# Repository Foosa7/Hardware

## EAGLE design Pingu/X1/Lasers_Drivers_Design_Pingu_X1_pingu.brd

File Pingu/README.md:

# Constant current sources #

* X1 - LED2001PHR, 4A, Buck

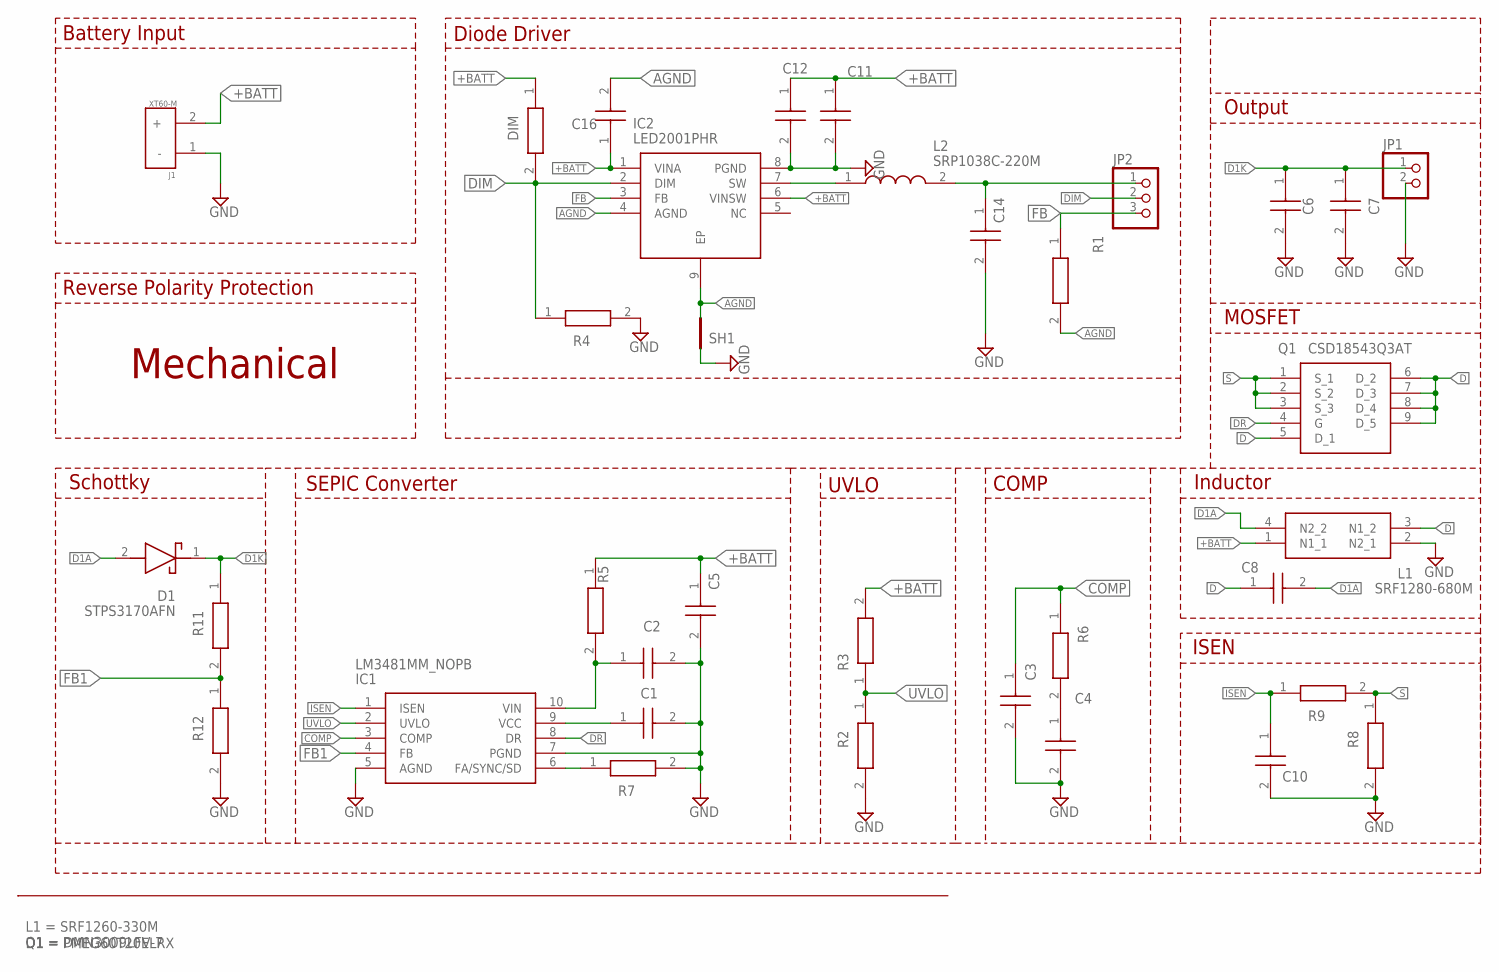
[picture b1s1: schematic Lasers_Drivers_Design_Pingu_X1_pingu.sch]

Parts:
C1, C2, C3, C4, C10, C11, C12: GCM0335C1H8R0DA16J; CAPC0603X33N
C5, C6, C7, C8, C14, C16: C1206C475K5RACTU; CAPC3216X180N
D1: STPS3170AFN; SODFL5226X110N
DIM: ERJ-3BWFR100V; RESC1608X55N
IC1: LM3481MM_NOPB; SOP50P490X110-10N
IC2: LED2001PHR; SOIC127P600X170-9N
J1: XT60-M; AMASS_XT60-M
JP1: PINHD-1X2; 1X02
JP2: PINHD-1X3; 1X03
L1: SRF1280-680M; SRF1280680M
L2: SRP1038C-220M; INDPM110100X420N
Q1: CSD18543Q3AT
R1, R2, R3, R4, R5, R6, R7, R8, R9, R11, R12: ERJ-3BWFR100V; RESC1608X55N
SH1: SHORTT5; SHORT_TOP-50

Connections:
+BATT: C5.1, C11.1, C12.1, C16.1, DIM.1, IC2.1 (VINA), IC2.6 (VINSW), J1.2 (+), L1.1 (N1_1), R3.2, R5.1
AGND: C16.2, IC2.4 (AGND), IC2.9 (EP), R1.2, SH1.2
COMP: C3.1, IC1.3 (COMP), R6.1
D: C8.1, L1.3 (N1_2), Q1.5 (D_1), Q1.6 (D_2), Q1.7 (D_3), Q1.8 (D_4), Q1.9 (D_5)
D1A: C8.2, D1.2 (A), L1.4 (N2_2)
D1K: C6.1, C7.1, D1.1 (K), JP1.1, R11.1
DIM: DIM.2, IC2.2 (DIM), JP2.2, R4.1
DR: IC1.8 (DR), Q1.4 (G)
FB: IC2.3 (FB), JP2.3, R1.1
FB1: IC1.4 (FB), R11.2, R12.1
GND: C1.2, C2.2, C3.2, C4.2, C5.2, C6.2, C7.2, C10.2, C11.2, C12.2, C14.2, IC1.5 (AGND), IC1.7 (PGND), IC2.8 (PGND), J1.1 (-), JP1.2, L1.2 (N2_1), R2.2, R4.2, R7.2, R8.2, R12.2, SH1.1
ISEN: C10.1, IC1.1 (ISEN), R9.1
unnamed: C1.1, IC1.9 (VCC)
unnamed: C4.1, R6.2
unnamed: IC2.7 (SW), L2.1
unnamed: IC1.6 (FA/SYNC/SD), R7.1
unnamed: C2.1, IC1.10 (VIN), R5.2
unnamed: C14.1, JP2.1, L2.2
S: Q1.1 (S_1), Q1.2 (S_2), Q1.3 (S_3), R8.1, R9.2
UVLO: IC1.2 (UVLO), R2.1, R3.1

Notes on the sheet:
L1 = SRF1260-330M
Battery Input
Reverse Polarity Protection
Q1 = DMN3009LFV-7
D1 = PMEG60T20ELRX
Diode Driver
Mechanical
UVLO
COMP
ISEN
SEPIC Converter
Inductor
MOSFET
Output
Schottky

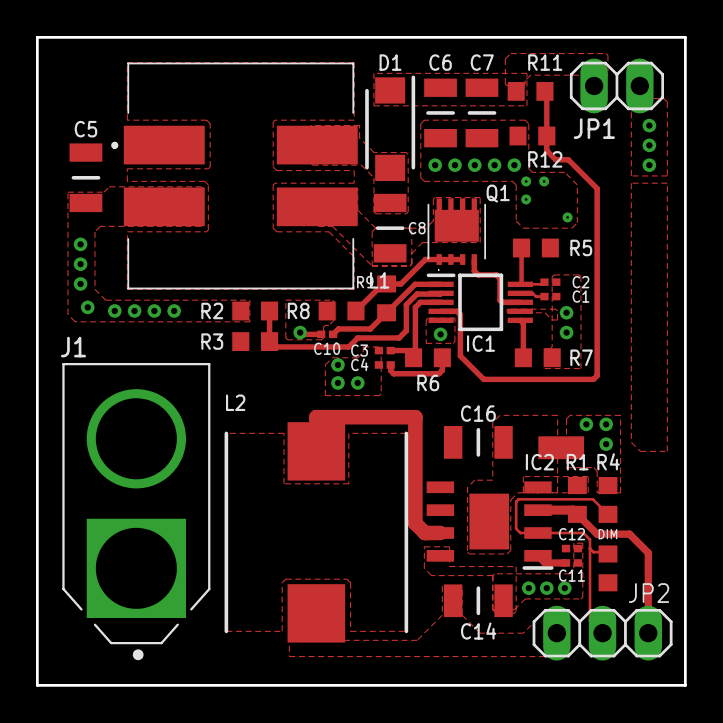
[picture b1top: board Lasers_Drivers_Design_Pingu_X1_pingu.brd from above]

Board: 2 copper layers, 36.0 x 36.0 mm, 35 parts (0 on the bottom side), 20 nets.
